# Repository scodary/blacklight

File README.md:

# blacklight
A flashlight which adjusts its color temperature to the body heat of the user.

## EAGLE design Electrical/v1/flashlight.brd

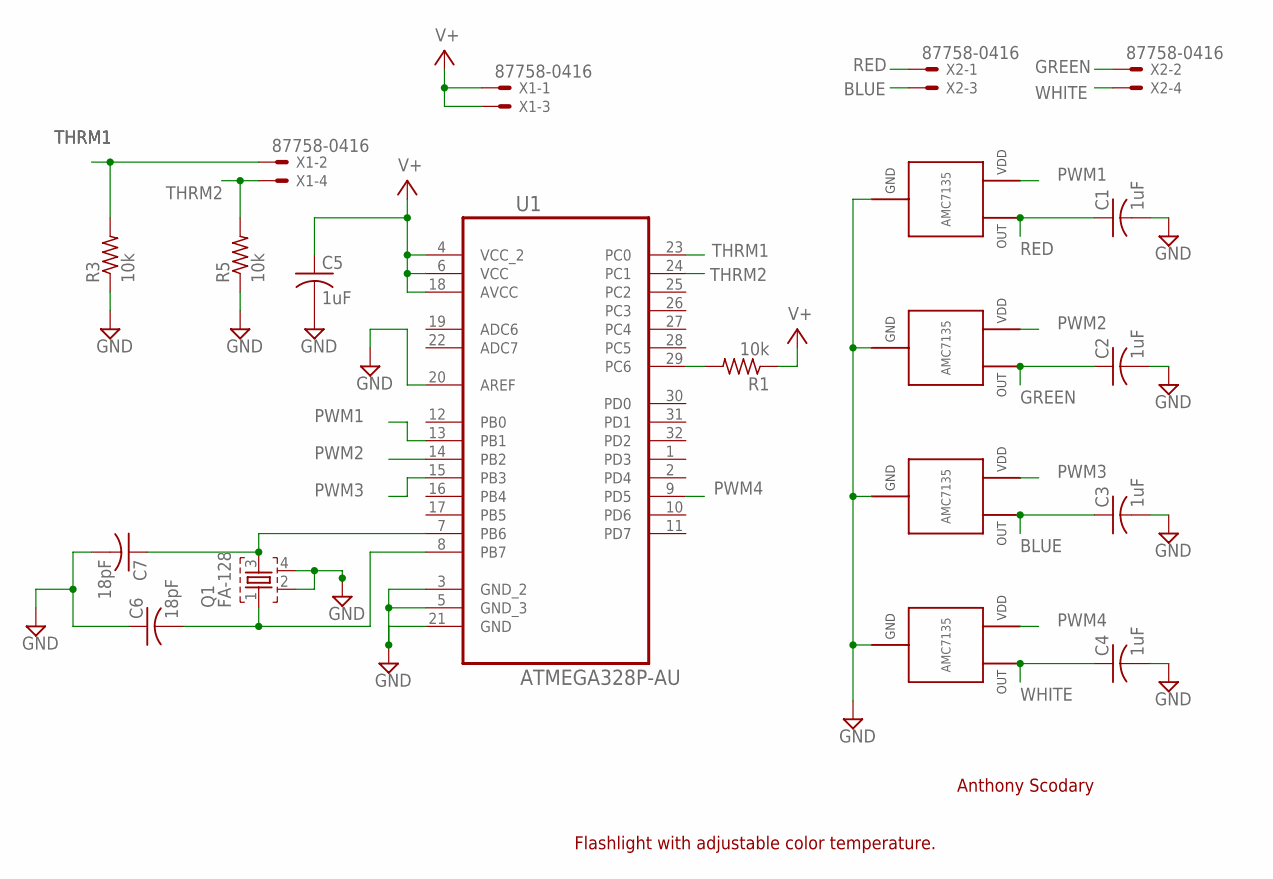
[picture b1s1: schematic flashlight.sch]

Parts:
C1, C2, C3, C4, C5: 1uF; C0805
C6, C7: 18pF; C0805
Q1: FA-128
R1, R3, R5: 10k; R0805
U1: ATMEGA328P-AU; QFP80P900X900X120-32N
U$1, U$2, U$3, U$4: AMC7135_CC_REGULATOR
X1, X2: 87758-0416

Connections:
BLUE: C3.1, U$3.OUT, X2.3
GND: C1.2, C2.2, C3.2, C4.2, C5.2, C6.1, C7.2, Q1.2, Q1.4, R3.1, R5.1, U1.3 (GND_2), U1.5 (GND_3), U1.20 (AREF), U1.21 (GND), U$1.GND2 (GND), U$1.GND3 (GND), U$2.GND2 (GND), U$2.GND3 (GND), U$3.GND2 (GND), U$3.GND3 (GND), U$4.GND2 (GND), U$4.GND3 (GND)
GREEN: C2.1, U$2.OUT, X2.2
unnamed: C6.2, Q1.1, U1.8 (PB7)
unnamed: C7.1, Q1.3, U1.7 (PB6)
unnamed: R1.2, U1.29 (PC6)
PWM1: U1.13 (PB1), U$1.VDD
PWM2: U1.14 (PB2), U$2.VDD
PWM3: U1.15 (PB3), U$3.VDD
PWM4: U1.9 (PD5), U$4.VDD
RED: C1.1, U$1.OUT, X2.1
THRM1: R3.2, U1.23 (PC0), X1.2
THRM2: R5.2, U1.24 (PC1), X1.4
V+: C5.1, R1.1, U1.4 (VCC_2), U1.6 (VCC), U1.18 (AVCC), X1.1, X1.3
WHITE: C4.1, U$4.OUT, X2.4

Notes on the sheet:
Anthony Scodary
Flashlight with adjustable color temperature.

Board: 2 copper layers, 18 parts (9 on the bottom side), 15 nets, no tracks yet.

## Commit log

2016-10-04 Initial Prototype
2016-10-04 Prototype (v1) Sketch
2016-10-04 Blackbody spectrum to LED value tool
2016-10-05 Datasheets
2016-10-06 Updated v1
    - Interpolated temperature
    - Dynamic brightness
    - Smoothed temperature reading
